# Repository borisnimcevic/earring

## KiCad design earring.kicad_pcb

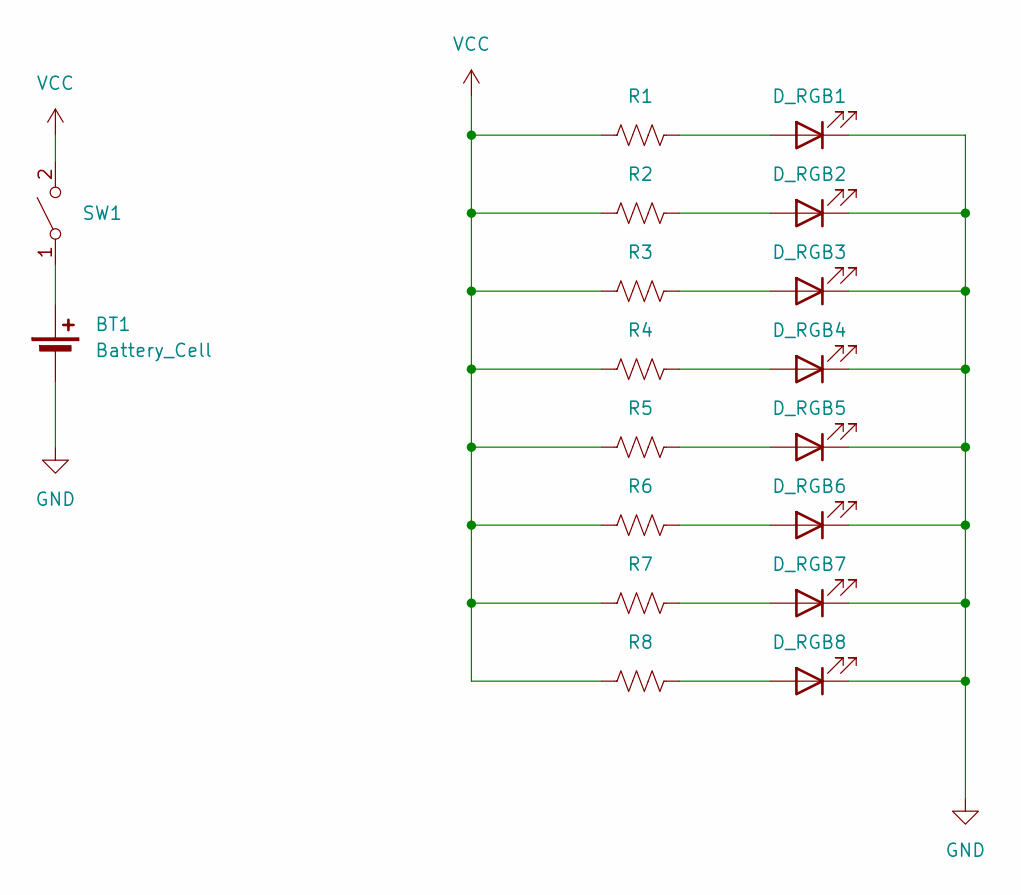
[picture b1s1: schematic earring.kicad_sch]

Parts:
BT1: Battery_Cell; BatteryHolder_LINX_BAT-HLD-012-SMT
D_RGB1, D_RGB2, D_RGB3, D_RGB4, D_RGB5, D_RGB6, D_RGB7, D_RGB8: 0807 RGB self flashing; 0807_RGB_LED
R1, R2, R3, R4, R5, R6, R7, R8: R_US; R_0805_2012Metric_Pad1.20x1.40mm_HandSolder
SW1: SW_SPST; SW_SPDT_PCM12

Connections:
GND: BT1.2 (-), D_RGB1.2 (K), D_RGB2.2 (K), D_RGB3.2 (K), D_RGB4.2 (K), D_RGB5.2 (K), D_RGB6.2 (K), D_RGB7.2 (K), D_RGB8.2 (K)
unnamed: BT1.1 (+), SW1.1 (A)
unnamed: D_RGB1.1 (A), R1.2
unnamed: D_RGB2.1 (A), R2.2
unnamed: D_RGB3.1 (A), R3.2
unnamed: D_RGB4.1 (A), R4.2
unnamed: D_RGB5.1 (A), R5.2
unnamed: D_RGB6.1 (A), R6.2
unnamed: D_RGB7.1 (A), R7.2
unnamed: D_RGB8.1 (A), R8.2
VCC: R1.1, R2.1, R3.1, R4.1, R5.1, R6.1, R7.1, R8.1, SW1.2 (B)

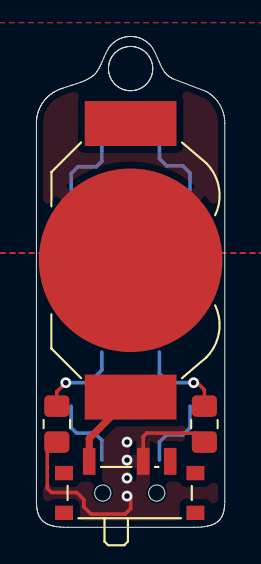
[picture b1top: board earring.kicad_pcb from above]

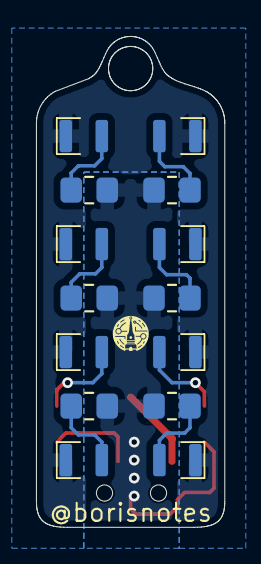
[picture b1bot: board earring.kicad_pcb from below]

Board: 2 copper layers, 10.5 x 27.3 mm, 18 parts (14 on the bottom side), 11 nets.
